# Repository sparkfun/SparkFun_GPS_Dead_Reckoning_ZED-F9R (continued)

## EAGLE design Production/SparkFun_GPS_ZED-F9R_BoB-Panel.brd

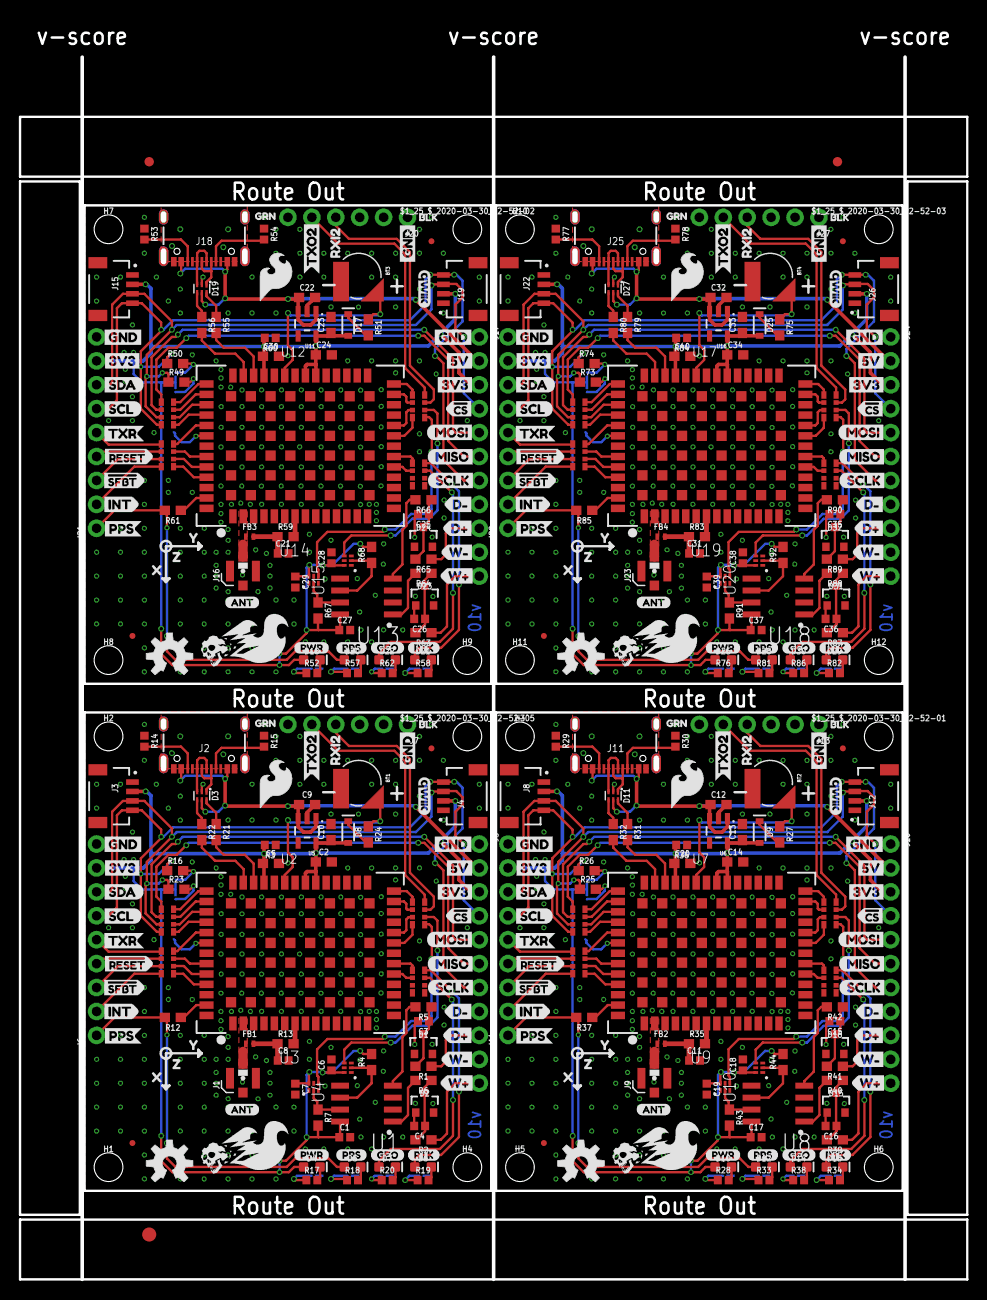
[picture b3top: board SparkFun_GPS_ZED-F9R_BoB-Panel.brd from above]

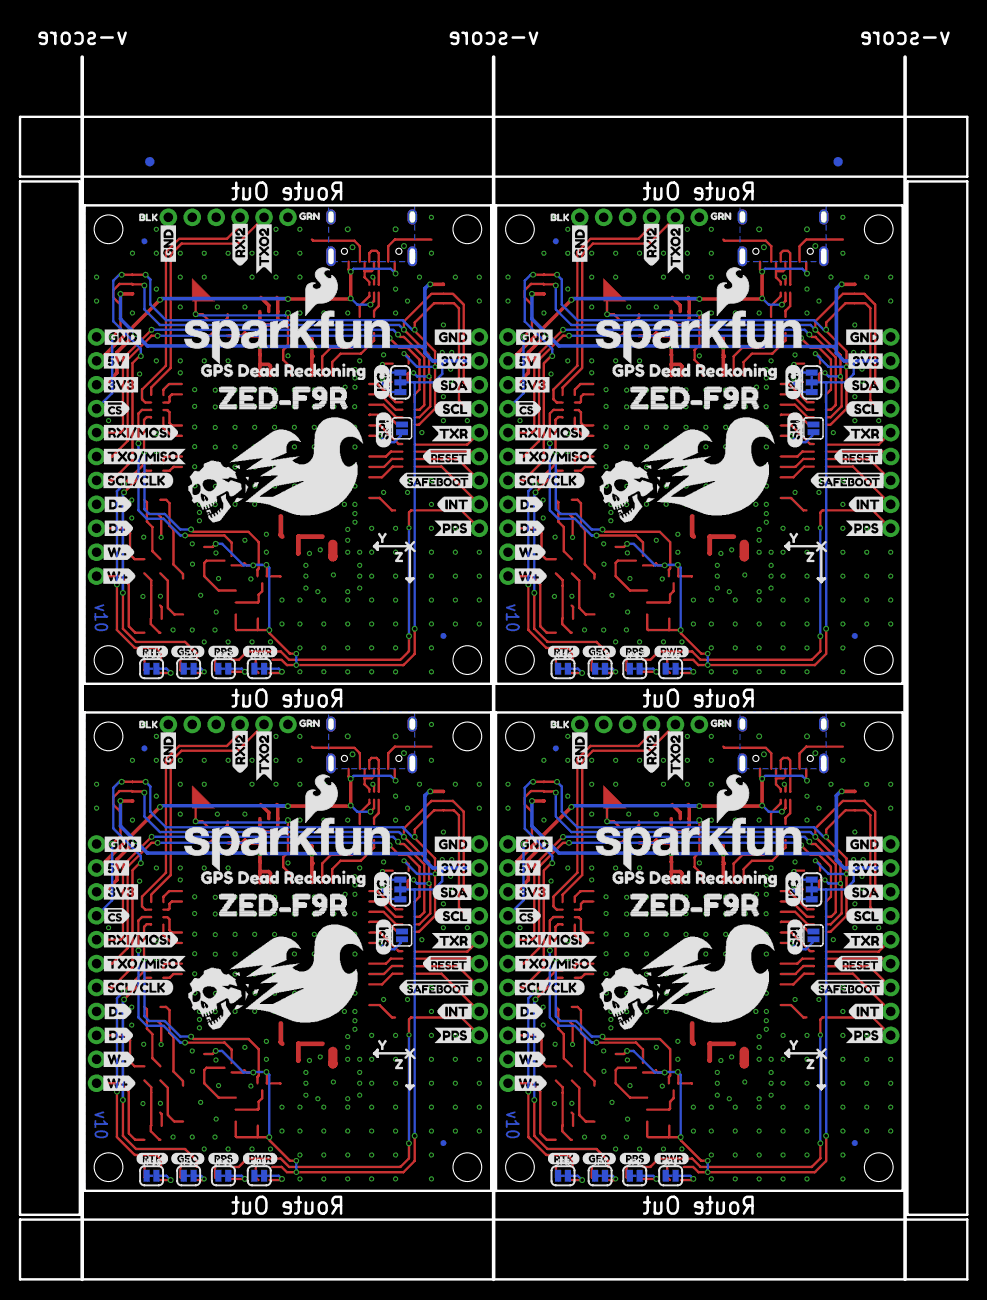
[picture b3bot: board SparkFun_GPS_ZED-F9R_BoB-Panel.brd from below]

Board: 2 copper layers, 100.6 x 129.8 mm, 581 parts (182 on the bottom side), 264 nets.

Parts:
$1_25_$_2020-03-30_22-52-01, $1_25_$_2020-03-30_22-52-02, $1_25_$_2020-03-30_22-52-03, $1_25_$_2020-03-30_22-52-05: STAND-OFFTIGHT; STAND-OFF-TIGHT
BT1, BT2, BT3, BT4: ML414H_IV01E_BATTERY; ML414H_IV01E
C1, C6, C7, C17, C18, C19, C27, C28, C29, C37, C38, C39: 0.1uF; 0402
C2, C5, C9, C10, C12, C13, C14, C20, C22, C23, C24, C30, C32, C33, C34, C40: 1.0uF; 0603
C3, C4, C15, C16, C25, C26, C35, C36: 1nF; 0402
C8, C11, C21, C31: 47pF; 0402
D1, D2, D15, D16, D23, D24, D31, D32: 15V; SOT23-3
D3, D11, D19, D27: PRTR5V0U2F; SOT886
D4, D10, D18, D26: RED; LED-0603
D5, D6, D7, D12, D13, D14, D20, D21, D22, D28, D29, D30: BLUE; LED-0603
D8, D9, D17, D25: 0.5A/40V/420mV; SOD-323
E$1, E$2, E$3, E$4: FIDUCIAL-1X2
E$5: FIDUCIAL-1.5X3
FB1, FB2, FB3, FB4: 120NH; 0402_MURATA
FD1, FD2, FD3, FD4, FD5, FD6, FD7, FD8, FD9, FD10, FD11, FD12, FD13, FD14, FD15, FD16: FIDUCIALUFIDUCIAL; FIDUCIAL-MICRO
H1, H2, H3, H4, H5, H6, H7, H8, H9, H10, H11, H12: STAND-OFFTIGHT; STAND-OFF-TIGHT
J1, J9, J16, J23: U.FL
J2, J11, J18, J25: USB-C-16P-2LAYER-PADS
J3, J4, J8, J12, J15, J19, J22, J26: QWIIC_RIGHT_ANGLE; JST04_1MM_RA
J5, J10, J17, J24: 1X11_NO_SILK
J6, J14, J21, J28: 1X09_NO_SILK
J7, J13, J20, J27: 1X06_NO_SILK
JP1, JP2, JP3, JP4, JP9, JP10, JP11, JP12, JP15, JP16, JP17, JP18, JP21, JP22, JP23, JP24: JUMPER-SMT_2_NC_TRACE_SILK; SMT-JUMPER_2_NC_TRACE_SILK
JP5, JP8, JP14, JP20: JUMPER-SMT_2_NO_SILK; SMT-JUMPER_2_NO_SILK
JP6, JP7, JP13, JP19: JUMPER-SMT_3_2-NC_TRACE_SILK; SMT-JUMPER_3_2-NC_TRACE_SILK
LOGO1, LOGO6, LOGO9, LOGO12: OSHW-LOGOM; OSHW-LOGO-M
LOGO2, LOGO5, LOGO8, LOGO11: QWIIC_LOGO_4MM; QWIIC_4MM
LOGO3, LOGO4, LOGO7, LOGO10: SFE_LOGO_NAME_FLAME.2_INCH; SFE_LOGO_NAME_FLAME_.2
R1, R2, R24, R27, R39, R41, R51, R63, R65, R75, R87, R89: 3.3k; 0603
R3, R36, R60, R84: 100K; 0402
R4, R7, R43, R44, R67, R68, R91, R92: 910; 0603
R5, R6, R40, R42, R64, R66, R88, R90: 470; 0603
R8, R9, R10, R11, R45, R46, R47, R48, R69, R70, R71, R72, R93, R94, R95, R96: 33; 1206_RA
R12, R13, R35, R37, R59, R61, R83, R85: 33; 0603
R14, R15, R29, R30, R53, R54, R77, R78: 5.1k; 0402
R16, R23, R25, R26, R49, R50, R73, R74: 2.2k; 0603
R17, R18, R19, R20, R28, R33, R34, R38, R52, R57, R58, R62, R76, R81, R82, R86: 1KOHM-0402-1/16W-1%; 0402
R21, R22, R31, R32, R55, R56, R79, R80: 27; 0603
U1, U8, U13, U18: DUAL-OPTO_HCPL-073L; SOP_8-PIN
U2, U7, U12, U17: U-BLOX_ZED_F9R; UBLOX_ZED_F9R
U3, U4, U9, U10, U14, U15, U19, U20: UHS_INVERTER_SCHMITT_TRIGGERSIP6; SIP6
U5, U6, U11, U16: 3.3V; SOT23-5
U$1, U$29, U$40, U$70, U$78, U$80, U$113, U$115, U$149, U$151, U$184, U$186, U$220, U$222, U$255, U$257: 3V3-04
U$2, U$15, U$31, U$34, U$41, U$71, U$79, U$81, U$83, U$114, U$116, U$126, U$150, U$152, U$154, U$185, U$187, U$197, U$221, U$223, U$225, U$256, U$258, U$268: GND-04
U$3, U$60, U$119, U$139, U$190, U$210, U$261, U$281: D#0
U$4, U$47, U$73, U$89, U$144, U$160, U$215, U$231: PPS8
U$5, U$48, U$74, U$90, U$145, U$161, U$216, U$232: PWR10
U$6, U$64, U$120, U$141, U$191, U$212, U$262, U$283: D#1
U$7, U$105, U$176, U$247: #RESET2
U$8, U$22, U$75, U$88, U$146, U$159, U$217, U$230: RTK9
U$9, U$61, U$121, U$140, U$192, U$211, U$263, U$282: W#2
U$10, U$65, U$122, U$142, U$193, U$213, U$264, U$284: W#3
U$11, U$33, U$82, U$123, U$153, U$194, U$224, U$265: 5V
U$12, U$124, U$195, U$266: INT1
U$13, U$125, U$196, U$267: PPS4
U$14, U$128, U$199, U$270: RXI22
U$16, U$36, U$85, U$127, U$156, U$198, U$227, U$269: TXO21
U$17, U$129, U$200, U$271: SCLK1
U$18, U$130, U$201, U$272: TXR0
U$19, U$20, U$132, U$133, U$203, U$204, U$274, U$275: DEAD#RECKONING#GPS#BOARD#SILK#FINAL#JPG
U$21, U$54, U$76, U$94, U$147, U$165, U$218, U$236: BLK2
U$23, U$53, U$77, U$93, U$148, U$164, U$219, U$235: GRN1
U$24, U$95, U$166, U$237: INT2
U$25, U$131, U$202, U$273: GPS_DEAD_RECKONING0
U$26, U$72, U$143, U$214: CS#-<]-04
U$27, U$96, U$167, U$238: PPS1
U$28, U$106, U$177, U$248: #SAFEBOOT3
U$30, U$98, U$169, U$240: RXI#MOSI0
U$32, U$134, U$205, U$276: X1
U$35, U$84, U$155, U$226: RXI28
U$37, U$99, U$170, U$241: TXO#MISO1
U$38, U$100, U$171, U$242: SCL#CLK2
U$39, U$101, U$172, U$243: SCL5
U$42, U$102, U$173, U$244: SDA4
U$43, U$103, U$174, U$245: TXR3
U$44, U$104, U$175, U$246: #RESET1
U$45, U$86, U$157, U$228: SPI4
U$46, U$87, U$158, U$229: I_SUPER2_C-()-04
U$49, U$91, U$162, U$233: ANT0
U$50, U$52, U$135, U$136, U$206, U$207, U$277, U$278: Y2
U$51, U$92, U$163, U$234: ZED#F9R0
U$55, U$107, U$178, U$249: #SFBT0
U$56, U$58, U$108, U$109, U$179, U$180, U$250, U$251: GEO1
U$57, U$63, U$137, U$138, U$208, U$209, U$279, U$280: Z0
U$59, U$97, U$168, U$239: CS#-[>-04
U$62, U$110, U$181, U$252: SFE_LOGO_FLAME_.2
U$66, U$117, U$188, U$259: MISO-(]-04
U$67, U$111, U$182, U$253: SCL-[)
U$68, U$112, U$183, U$254: SDA-[)
U$69, U$118, U$189, U$260: MOSI-(]-04

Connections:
3.3V: C1.1, C2.1, C5.1, C6.1, C7.1, C10.1, D4.A, D8.A, J3.2, J4.2, J5.3, J6.8, JP6.2, R3.2, R4.2, R7.2, U1.P8, U2.P33, U2.P34, U2.P38, U3.P6, U4.P6, U5.5
3.3V1: C13.1, C14.1, C17.1, C18.1, C19.1, C20.1, D9.A, D10.A, J8.2, J10.3, J12.2, J14.8, JP7.2, R36.2, R43.2, R44.2, U6.5, U7.P33, U7.P34, U7.P38, U8.P8, U9.P6, U10.P6
3.3V2: C23.1, C24.1, C27.1, C28.1, C29.1, C30.1, D17.A, D18.A, J15.2, J17.3, J19.2, J21.8, JP13.2, R60.2, R67.2, R68.2, U11.5, U12.P33, U12.P34, U12.P38, U13.P8, U14.P6, U15.P6
3.3V3: C33.1, C34.1, C37.1, C38.1, C39.1, C40.1, D25.A, D26.A, J22.2, J24.3, J26.2, J28.8, JP19.2, R84.2, R91.2, R92.2, U16.5, U17.P33, U17.P34, U17.P38, U18.P8, U19.P6, U20.P6
!RESET: J6.4, R8.P2
!RESET1: J14.4, R46.P2
!RESET2: J21.4, R70.P2
!RESET3: J28.4, R94.P2
!SAFEBOOT: J6.3, R8.P3
!SAFEBOOT1: J14.3, R46.P3
!SAFEBOOT2: J21.3, R70.P3
!SAFEBOOT3: J28.3, R94.P3
DIR+: J5.9, R1.1
DIR+1: J10.9, R41.1
DIR+2: J17.9, R65.1
DIR+3: J24.9, R89.1
DIR_IN: R5.2, U1.P4
DIR_IN1: R42.2, U8.P4
DIR_IN2: R66.2, U13.P4
DIR_IN3: R90.2, U18.P4
DIR_OUT: R10.P6, U4.P4
DIR_OUT1: R47.P6, U10.P4
DIR_OUT2: R71.P6, U15.P4
DIR_OUT3: R95.P6, U20.P4
DIR_SCHMITT: R4.1, U1.P6, U4.P2
DIR_SCHMITT1: R44.1, U8.P6, U10.P2
DIR_SCHMITT2: R68.1, U13.P6, U15.P2
DIR_SCHMITT3: R92.1, U18.P6, U20.P2
DMINUS: R21.2, U2.P39
DMINUS1: R31.2, U7.P39
DMINUS2: R55.2, U12.P39
DMINUS3: R79.2, U17.P39
DPLUS: R22.2, U2.P40
DPLUS1: R32.2, U7.P40
DPLUS2: R56.2, U12.P40
DPLUS3: R80.2, U17.P40
D_SEL: JP5.1, U2.P47
D_SEL1: JP8.1, U7.P47
D_SEL2: JP14.1, U12.P47
D_SEL3: JP20.1, U17.P47
GEOF_STAT: D7.A, R11.P7
GEOF_STAT1: D14.A, R48.P7
GEOF_STAT2: D22.A, R72.P7
GEOF_STAT3: D30.A, R96.P7
GND: BT1.-, C1.2, C2.2, C3.2, C4.2, C5.2, C6.2, C7.2, C8.2, C9.2, C10.2, D1.1, D2.1, D3.2, J1.1, J1.2, J2.GND, J2.GND2, J3.1, J4.1, J5.1, J5.8, J5.10, J6.9, J7.1, JP1.1, JP2.1, JP3.1, JP4.1, JP5.2, R3.1, R14.1, R15.1, U1.P2, U1.P3, U1.P5, U2.G1, U2.G2, U2.G3, U2.G4, U2.G5, U2.G6, U2.G7, U2.G8, U2.G9, U2.G10, U2.G11, U2.G12, U2.G13, U2.G14, U2.G15, U2.G16, U2.G17, U2.G18, U2.G19, U2.G20, U2.G21, U2.G22, U2.G23, U2.G24, U2.G25, U2.G26, U2.G27, U2.G28, U2.G29, U2.G30, U2.G31, U2.G32, U2.G33, U2.G34, U2.G35, U2.G36, U2.G37, U2.G38, U2.G39, U2.G40, U2.G41, U2.G42, U2.G43, U2.G44, U2.G45, U2.G46, U2.G47, U2.G48, U2.P1, U2.P3, U2.P12, U2.P14, U2.P32, U2.P37, U2.P41, U2.P48, U3.P3, U4.P3, U5.2
GND1: BT2.-, C11.2, C12.2, C13.2, C14.2, C15.2, C16.2, C17.2, C18.2, C19.2, C20.2, D11.2, D15.1, D16.1, J8.1, J9.1, J9.2, J10.1, J10.8, J10.10, J11.GND, J11.GND2, J12.1, J13.1, J14.9, JP8.2, JP9.1, JP10.1, JP11.1, JP12.1, R29.1, R30.1, R36.1, U6.2, U7.G1, U7.G2, U7.G3, U7.G4, U7.G5, U7.G6, U7.G7, U7.G8, U7.G9, U7.G10, U7.G11, U7.G12, U7.G13, U7.G14, U7.G15, U7.G16, U7.G17, U7.G18, U7.G19, U7.G20, U7.G21, U7.G22, U7.G23, U7.G24, U7.G25, U7.G26, U7.G27, U7.G28, U7.G29, U7.G30, U7.G31, U7.G32, U7.G33, U7.G34, U7.G35, U7.G36, U7.G37, U7.G38, U7.G39, U7.G40, U7.G41, U7.G42, U7.G43, U7.G44, U7.G45, U7.G46, U7.G47, U7.G48, U7.P1, U7.P3, U7.P12, U7.P14, U7.P32, U7.P37, U7.P41, U7.P48, U8.P2, U8.P3, U8.P5, U9.P3, U10.P3
GND2: BT3.-, C21.2, C22.2, C23.2, C24.2, C25.2, C26.2, C27.2, C28.2, C29.2, C30.2, D19.2, D23.1, D24.1, J15.1, J16.1, J16.2, J17.1, J17.8, J17.10, J18.GND, J18.GND2, J19.1, J20.1, J21.9, JP14.2, JP15.1, JP16.1, JP17.1, JP18.1, R53.1, R54.1, R60.1, U11.2, U12.G1, U12.G2, U12.G3, U12.G4, U12.G5, U12.G6, U12.G7, U12.G8, U12.G9, U12.G10, U12.G11, U12.G12, U12.G13, U12.G14, U12.G15, U12.G16, U12.G17, U12.G18, U12.G19, U12.G20, U12.G21, U12.G22, U12.G23, U12.G24, U12.G25, U12.G26, U12.G27, U12.G28, U12.G29, U12.G30, U12.G31, U12.G32, U12.G33, U12.G34, U12.G35, U12.G36, U12.G37, U12.G38, U12.G39, U12.G40, U12.G41, U12.G42, U12.G43, U12.G44, U12.G45, U12.G46, U12.G47, U12.G48, U12.P1, U12.P3, U12.P12, U12.P14, U12.P32, U12.P37, U12.P41, U12.P48, U13.P2, U13.P3, U13.P5, U14.P3, U15.P3
GND3: BT4.-, C31.2, C32.2, C33.2, C34.2, C35.2, C36.2, C37.2, C38.2, C39.2, C40.2, D27.2, D31.1, D32.1, J22.1, J23.1, J23.2, J24.1, J24.8, J24.10, J25.GND, J25.GND2, J26.1, J27.1, J28.9, JP20.2, JP21.1, JP22.1, JP23.1, JP24.1, R77.1, R78.1, R84.1, U16.2, U17.G1, U17.G2, U17.G3, U17.G4, U17.G5, U17.G6, U17.G7, U17.G8, U17.G9, U17.G10, U17.G11, U17.G12, U17.G13, U17.G14, U17.G15, U17.G16, U17.G17, U17.G18, U17.G19, U17.G20, U17.G21, U17.G22, U17.G23, U17.G24, U17.G25, U17.G26, U17.G27, U17.G28, U17.G29, U17.G30, U17.G31, U17.G32, U17.G33, U17.G34, U17.G35, U17.G36, U17.G37, U17.G38, U17.G39, U17.G40, U17.G41, U17.G42, U17.G43, U17.G44, U17.G45, U17.G46, U17.G47, U17.G48, U17.P1, U17.P3, U17.P12, U17.P14, U17.P32, U17.P37, U17.P41, U17.P48, U18.P2, U18.P3, U18.P5, U19.P3, U20.P3
INT: J6.2, R8.P4
INT1: J14.2, R46.P4
INT2: J21.2, R70.P4
INT3: J28.2, R94.P4
unnamed: JP6.1, R23.2
unnamed: D8.C, R24.2
unnamed: JP6.3, R16.2
unnamed: D4.C, R17.2
unnamed: C8.1, FB1.P2, R13.1
unnamed: D3.3, J2.A6, J2.B6
unnamed: D3.1, J2.A7, J2.B7
unnamed: JP1.2, R17.1
unnamed: D3.6, R21.1
unnamed: D3.4, R22.1
unnamed: R8.P7, U2.P49
unnamed: R8.P5, U2.P51
unnamed: D9.C, R27.2
unnamed: J2.B5, R14.2
unnamed: J2.A5, R15.2
unnamed: R9.P6, U2.P44
unnamed: R9.P5, U2.P45
unnamed: R8.P8, U2.P46
unnamed: R9.P8, U2.P42
unnamed: R9.P7, U2.P43
unnamed: R10.P1, U2.P27
unnamed: JP3.2, R19.1
unnamed: JP2.2, R18.1
unnamed: D5.C, R18.2
unnamed: D6.C, R19.2
unnamed: R10.P2, U2.P26
unnamed: R11.P2, U2.P19
unnamed: R11.P1, U2.P20
unnamed: R12.1, U2.P53
unnamed: R8.P6, U2.P50
unnamed: R10.P4, U2.P22
unnamed: R10.P3, U2.P23
unnamed: JP4.2, R20.1
unnamed: D7.C, R20.2
unnamed: C4.1, D2.3, R2.2, R6.1
unnamed: JP7.1, R25.2
unnamed: C3.1, D1.3, R1.2, R5.1
unnamed: JP7.3, R26.2
unnamed: J11.B5, R29.2
unnamed: J11.A5, R30.2
unnamed: JP10.2, R34.1
unnamed: JP11.2, R33.1
unnamed: D12.C, R33.2
unnamed: D13.C, R34.2
unnamed: D10.C, R28.2
unnamed: JP9.2, R28.1
unnamed: C11.1, FB2.P2, R35.1
unnamed: D11.3, J11.A6, J11.B6
unnamed: D11.1, J11.A7, J11.B7
unnamed: D11.6, R31.1
unnamed: D11.4, R32.1
unnamed: R46.P7, U7.P49
unnamed: R46.P5, U7.P51
unnamed: R45.P6, U7.P44
unnamed: R45.P5, U7.P45
unnamed: R46.P8, U7.P46
unnamed: R45.P8, U7.P42
unnamed: R45.P7, U7.P43
unnamed: R47.P1, U7.P27
unnamed: R47.P2, U7.P26
unnamed: R48.P2, U7.P19
unnamed: R48.P1, U7.P20
unnamed: R37.1, U7.P53
unnamed: R46.P6, U7.P50
unnamed: R47.P4, U7.P22
unnamed: R47.P3, U7.P23
unnamed: JP12.2, R38.1
unnamed: D14.C, R38.2
unnamed: C16.1, D15.3, R39.2, R40.1
unnamed: C15.1, D16.3, R41.2, R42.1
unnamed: D17.C, R51.2
unnamed: JP13.1, R49.2
unnamed: JP13.3, R50.2
unnamed: J18.B5, R53.2
unnamed: J18.A5, R54.2
unnamed: JP16.2, R58.1
unnamed: JP17.2, R57.1
unnamed: D20.C, R57.2
unnamed: D21.C, R58.2
unnamed: D18.C, R52.2
unnamed: JP15.2, R52.1
unnamed: C21.1, FB3.P2, R59.1
unnamed: D19.3, J18.A6, J18.B6
unnamed: D19.1, J18.A7, J18.B7
unnamed: D19.6, R55.1
unnamed: D19.4, R56.1
unnamed: R70.P7, U12.P49
unnamed: R70.P5, U12.P51
unnamed: R69.P6, U12.P44
unnamed: R69.P5, U12.P45
unnamed: R70.P8, U12.P46
unnamed: R69.P8, U12.P42
unnamed: R69.P7, U12.P43
unnamed: R71.P1, U12.P27
unnamed: R71.P2, U12.P26
unnamed: R72.P2, U12.P19
unnamed: R72.P1, U12.P20
unnamed: R61.1, U12.P53
unnamed: R70.P6, U12.P50
unnamed: R71.P4, U12.P22
unnamed: R71.P3, U12.P23
unnamed: JP18.2, R62.1
unnamed: D22.C, R62.2
unnamed: C26.1, D23.3, R63.2, R64.1
unnamed: C25.1, D24.3, R65.2, R66.1
unnamed: D25.C, R75.2
unnamed: JP19.1, R73.2
unnamed: JP19.3, R74.2
unnamed: J25.B5, R77.2
unnamed: J25.A5, R78.2
unnamed: JP22.2, R82.1
unnamed: JP23.2, R81.1
unnamed: D28.C, R81.2
unnamed: D29.C, R82.2
unnamed: D26.C, R76.2
unnamed: JP21.2, R76.1
unnamed: C31.1, FB4.P2, R83.1
unnamed: D27.3, J25.A6, J25.B6
unnamed: D27.1, J25.A7, J25.B7
unnamed: D27.6, R79.1
unnamed: D27.4, R80.1
unnamed: R94.P7, U17.P49
unnamed: R94.P5, U17.P51
unnamed: R93.P6, U17.P44
unnamed: R93.P5, U17.P45
unnamed: R94.P8, U17.P46
unnamed: R93.P8, U17.P42
unnamed: R93.P7, U17.P43
unnamed: R95.P1, U17.P27
unnamed: R95.P2, U17.P26
unnamed: R96.P2, U17.P19
unnamed: R96.P1, U17.P20
unnamed: R85.1, U17.P53
unnamed: R94.P6, U17.P50
unnamed: R95.P4, U17.P22
unnamed: R95.P3, U17.P23
unnamed: JP24.2, R86.1
unnamed: D30.C, R86.2
unnamed: C36.1, D31.3, R87.2, R88.1
unnamed: C35.1, D32.3, R89.2, R90.1
PPS: D5.A, J6.1, R12.2
PPS1: D12.A, J14.1, R37.2
PPS2: D20.A, J21.1, R61.2
PPS3: D28.A, J28.1, R85.2
RF_IN: FB1.P1, J1.FEED, U2.P2
RF_IN1: FB2.P1, J9.FEED, U7.P2
RF_IN2: FB3.P1, J16.FEED, U12.P2
RF_IN3: FB4.P1, J23.FEED, U17.P2
RTK_STAT: D6.A, R11.P8
RTK_STAT1: D13.A, R48.P8
RTK_STAT2: D21.A, R72.P8
RTK_STAT3: D29.A, R96.P8
RXI1: J13.4, R47.P7
RXI2: J7.4, R10.P7
RXI3: J20.4, R71.P7
RXI4: J27.4, R95.P7
RXI/MOSI: J5.5, R9.P2
RXI/MOSI1: J10.5, R45.P2
RXI/MOSI2: J17.5, R69.P2
RXI/MOSI3: J24.5, R93.P2
SCL/CLK: J3.4, J4.4, J5.7, J6.6, R9.P4, R16.1
SCL/CLK1: J8.4, J10.7, J12.4, J14.6, R26.1, R45.P4
SCL/CLK2: J15.4, J17.7, J19.4, J21.6, R50.1, R69.P4
SCL/CLK3: J22.4, J24.7, J26.4, J28.6, R74.1, R93.P4
SDA/!CS: J3.3, J4.3, J5.4, J6.7, R9.P3, R23.1
SDA/!CS1: J8.3, J10.4, J12.3, J14.7, R25.1, R45.P3
SDA/!CS2: J15.3, J17.4, J19.3, J21.7, R49.1, R69.P3
SDA/!CS3: J22.3, J24.4, J26.3, J28.7, R73.1, R93.P3
SHIELD: J2.SHLD1, J2.SHLD2, J2.SHLD3, J2.SHLD4
SHIELD1: J11.SHLD1, J11.SHLD2, J11.SHLD3, J11.SHLD4
SHIELD2: J18.SHLD1, J18.SHLD2, J18.SHLD3, J18.SHLD4
SHIELD3: J25.SHLD1, J25.SHLD2, J25.SHLD3, J25.SHLD4
TXO1: J13.5, R47.P8
TXO2: J7.5, R10.P8
TXO3: J20.5, R71.P8
TXO4: J27.5, R95.P8
TXO/MISO: J5.6, R9.P1
TXO/MISO1: J10.6, R45.P1
TXO/MISO2: J17.6, R69.P1
TXO/MISO3: J24.6, R93.P1
TX_READY: J6.5, R8.P1
TX_READY1: J14.5, R46.P1
TX_READY2: J21.5, R70.P1
TX_READY3: J28.5, R94.P1
VIN: C9.1, D3.5, J2.VBUS1, J2.VBUS2, J5.2, U5.1, U5.3
VIN1: C12.1, D11.5, J10.2, J11.VBUS1, J11.VBUS2, U6.1, U6.3
VIN2: C22.1, D19.5, J17.2, J18.VBUS1, J18.VBUS2, U11.1, U11.3
VIN3: C32.1, D27.5, J24.2, J25.VBUS1, J25.VBUS2, U16.1, U16.3
V_BATT: BT1.+, R24.1, U2.P36
V_BATT1: BT2.+, R27.1, U7.P36
V_BATT2: BT3.+, R51.1, U12.P36
V_BATT3: BT4.+, R75.1, U17.P36
V_RF: R13.2, U2.P7
V_RF1: R35.2, U7.P7
V_RF2: R59.2, U12.P7
V_RF3: R83.2, U17.P7
WT+: J5.11, R2.1
WT+1: J10.11, R39.1
WT+2: J17.11, R63.1
WT+3: J24.11, R87.1
WT_IN: R6.2, U1.P1
WT_IN1: R40.2, U8.P1
WT_IN2: R64.2, U13.P1
WT_IN3: R88.2, U18.P1
WT_OUT: R10.P5, U3.P4
WT_OUT1: R47.P5, U9.P4
WT_OUT2: R71.P5, U14.P4
WT_OUT3: R95.P5, U19.P4
WT_SCHMITT: R7.1, U1.P7, U3.P2
WT_SCHMITT1: R43.1, U8.P7, U9.P2
WT_SCHMITT2: R67.1, U13.P7, U14.P2
WT_SCHMITT3: R91.1, U18.P7, U19.P2

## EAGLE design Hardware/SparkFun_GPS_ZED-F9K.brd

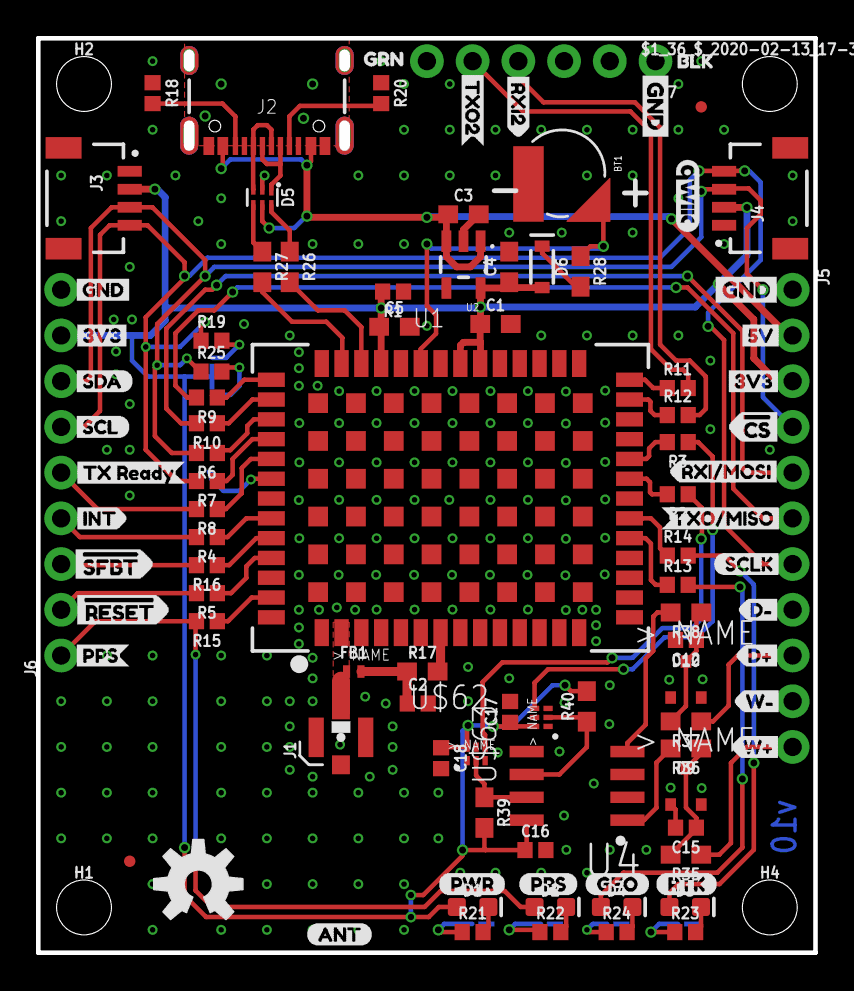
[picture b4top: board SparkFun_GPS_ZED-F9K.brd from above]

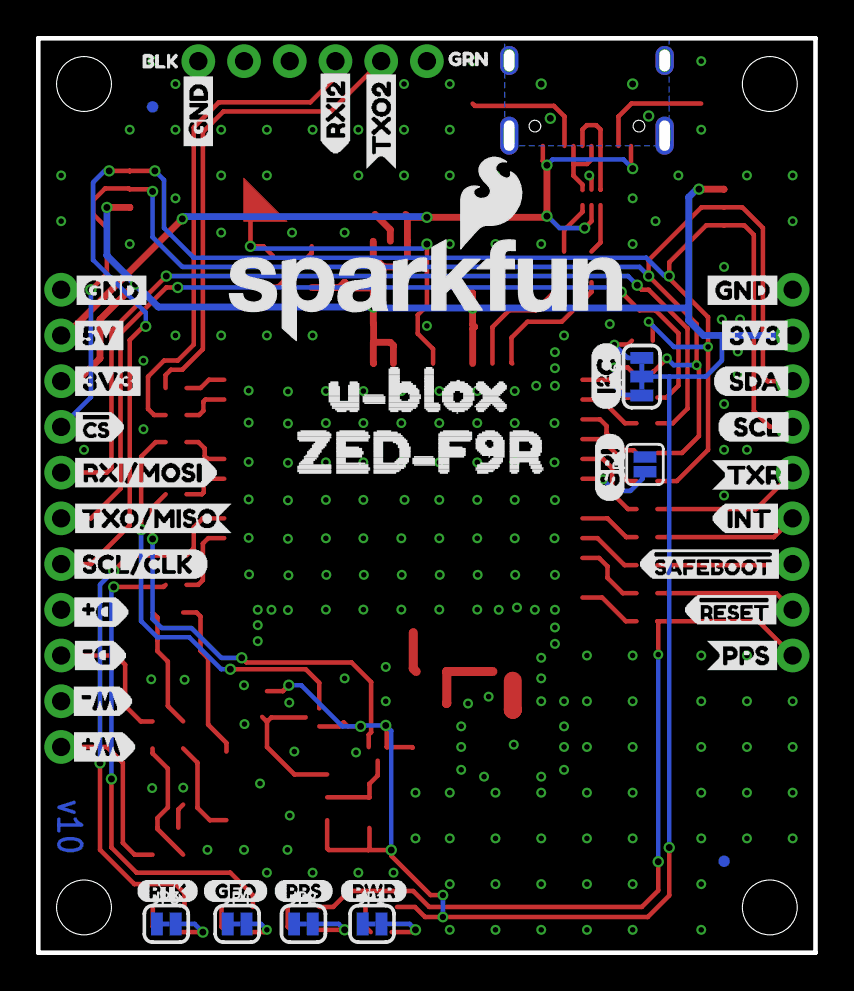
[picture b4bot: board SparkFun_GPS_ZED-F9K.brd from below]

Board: 2 copper layers, 43.2 x 50.8 mm, 147 parts (42 on the bottom side), 66 nets.

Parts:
$1_36_$_2020-02-13_17-32-45: STAND-OFFTIGHT; STAND-OFF-TIGHT
BT1: ML414H_IV01E_BATTERY; ML414H_IV01E
C1, C3, C4, C5: 1.0uF; 0603
C2: 47pF; 0402
C12, C15: 1nF; 0402
C16, C17, C18: 0.1uF; 0402
D1: RED; LED-0603
D2, D3, D4: BLUE; LED-0603
D5: PRTR5V0U2F; SOT886
D6: 0.5A/40V/420mV; SOD-323
D9, D10: 0.5A/40V/420mV; SOT23_BZX
FB1: 120NH; 0402_MURATA
FD1, FD2, FD3, FD4: FIDUCIALUFIDUCIAL; FIDUCIAL-MICRO
FRAME1: FRAME-LEDGER; CREATIVE_COMMONS
H1, H2, H4: STAND-OFFTIGHT; STAND-OFF-TIGHT
J1: U.FL
J2: USB-C-16P-2LAYER-PADS
J3, J4: QWIIC_RIGHT_ANGLE; JST04_1MM_RA
J5: 1X11_NO_SILK
J6: 1X09_NO_SILK
J7: 1X06_NO_SILK
JP1, JP2, JP3, JP4: JUMPER-SMT_2_NC_TRACE_SILK; SMT-JUMPER_2_NC_TRACE_SILK
JP5: JUMPER-SMT_2_NO_SILK; SMT-JUMPER_2_NO_SILK
JP6: JUMPER-SMT_3_2-NC_TRACE_SILK; SMT-JUMPER_3_2-NC_TRACE_SILK
LOGO1: OSHW-LOGOM; OSHW-LOGO-M
LOGO2: QWIIC_LOGO_4MM; QWIIC_4MM
LOGO3: SFE_LOGO_NAME_FLAME.2_INCH; SFE_LOGO_NAME_FLAME_.2
R1: 100K; 0402
R2, R3, R4, R5, R6, R7, R8, R9, R10, R11, R12, R13, R14, R15, R16: 33; 0402
R17: 33; 0603
R18, R20: 5.1k; 0402
R19, R25: 2.2K; 0402
R21, R22, R23, R24: 1KOHM-0402-1/16W-1%; 0402
R26, R27: 27; 0603
R28, R35, R37: 3.3k; 0603
R36, R38: 470; 0603
R39, R40: 910; 0603
U1: UBLOX_ZED_F9R
U2: 3.3V; SOT23-5
U4: HCPL-270L; SOP_8-PIN
U$1, U$24: INT2
U$2: PPS4
U$3, U$19: 3V32
U$4, U$47: PPS8
U$5, U$48: PWR10
U$6: GND3
U$7: #RESET2
U$8, U$22: RTK9
U$9: RXI#MOSI5
U$10, U$60: D#0
U$11: SCL0
U$12: SDA1
U$13, U$61: D#1
U$14: RXI22
U$15: TXO#MISO6
U$16: TX_READY0
U$17, U$20: GND-03
U$18: 5V0
U$21, U$54: BLK2
U$23, U$53: GRN1
U$25, U$36: TXO21
U$26: CS#-<]-04
U$27: PPS1
U$28: #SAFEBOOT3
U$29, U$40: 3V3-04
U$30: RXI#MOSI0
U$31, U$34, U$41: GND-04
U$32, U$64: W#2
U$33: 5V
U$35: RXI28
U$37: TXO#MISO1
U$38: SCL#CLK2
U$39: SCL5
U$42: SDA4
U$43: TXR3
U$44: #RESET1
U$45: SPI4
U$46: I_SUPER2_C-()-04
U$49: ANT0
U$50, U$65: W#3
U$51: ZED#F9R0
U$52: U#BLOX1
U$55: #SFBT0
U$56, U$58: GEO1
U$57: SCLK2
U$59: CS#-[>-04
U$62, U$63: UHS_INVERTER_SCHMITT_TRIGGERSIP6; SIP6

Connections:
3.3V: C1.1, C4.1, C5.1, C16.1, C17.1, C18.1, D1.A, D6.A, J3.2, J4.2, J5.3, J6.8, JP6.2, R1.2, R39.2, R40.2, U1.P33, U1.P34, U1.P38, U2.5, U4.P8, U$62.P6, U$63.P6
!RESET: J6.4, R4.2
!SAFEBOOT: J6.3, R16.2
DIR+: J5.9, R37.1
DIR_IN: R38.2, U4.P4
DIR_OUT: R3.1, U$63.P4
DIR_SCHMITT: R40.1, U4.P6, U$63.P2
DMINUS: R26.2, U1.P39
DPLUS: R27.2, U1.P40
D_SEL: JP5.1, U1.P47
GEOF_STAT: D4.A, R13.2
GND: BT1.-, C1.2, C2.2, C3.2, C4.2, C5.2, C12.2, C15.2, C16.2, C17.2, C18.2, D5.2, D9.P1, D10.P1, J1.1, J1.2, J2.GND, J2.GND2, J3.1, J4.1, J5.1, J5.8, J5.10, J6.9, J7.1, JP1.1, JP2.1, JP3.1, JP4.1, JP5.2, R1.1, R18.1, R20.1, U1.G1, U1.G2, U1.G3, U1.G4, U1.G5, U1.G6, U1.G7, U1.G8, U1.G9, U1.G10, U1.G11, U1.G12, U1.G13, U1.G14, U1.G15, U1.G16, U1.G17, U1.G18, U1.G19, U1.G20, U1.G21, U1.G22, U1.G23, U1.G24, U1.G25, U1.G26, U1.G27, U1.G28, U1.G29, U1.G30, U1.G31, U1.G32, U1.G33, U1.G34, U1.G35, U1.G36, U1.G37, U1.G38, U1.G39, U1.G40, U1.G41, U1.G42, U1.G43, U1.G44, U1.G45, U1.G46, U1.G47, U1.G48, U1.P1, U1.P3, U1.P12, U1.P14, U1.P32, U1.P37, U1.P41, U1.P48, U2.2, U4.P2, U4.P3, U4.P5, U$62.P3, U$63.P3
INT: J6.2, R5.2
unnamed: JP6.1, R25.2
unnamed: D6.C, R28.2
unnamed: JP6.3, R19.2
unnamed: D1.C, R21.2
unnamed: C2.1, FB1.P2, R17.1
unnamed: D5.3, J2.A6, J2.B6
unnamed: D5.1, J2.A7, J2.B7
unnamed: JP1.2, R21.1
unnamed: D5.6, R26.1
unnamed: D5.4, R27.1
unnamed: R4.1, U1.P49
unnamed: R5.1, U1.P51
unnamed: J2.B5, R18.2
unnamed: J2.A5, R20.2
unnamed: R6.1, U1.P44
unnamed: R7.1, U1.P45
unnamed: R8.1, U1.P46
unnamed: R9.1, U1.P42
unnamed: R10.1, U1.P43
unnamed: R11.1, U1.P27
unnamed: JP3.2, R23.1
unnamed: JP2.2, R22.1
unnamed: D2.C, R22.2
unnamed: D3.C, R23.2
unnamed: R12.1, U1.P26
unnamed: R13.1, U1.P19
unnamed: R14.1, U1.P20
unnamed: R15.1, U1.P53
unnamed: R16.1, U1.P50
unnamed: R2.2, U1.P22
unnamed: R3.2, U1.P23
unnamed: JP4.2, R24.1
unnamed: D4.C, R24.2
unnamed: C15.1, D9.P3, R35.2, R36.1
unnamed: C12.1, D10.P3, R37.2, R38.1
PPS: D2.A, J6.1, R15.2
RF_IN: FB1.P1, J1.FEED, U1.P2
RTK_STAT: D3.A, R14.2
RXI2: J7.4, R12.2
RXI/MOSI: J5.5, R10.2
SCL/CLK: J3.4, J4.4, J5.7, J6.6, R7.2, R19.1
SDA/!CS: J3.3, J4.3, J5.4, J6.7, R6.2, R25.1
SHIELD: J2.SHLD1, J2.SHLD2, J2.SHLD3, J2.SHLD4
TXO2: J7.5, R11.2
TXO/MISO: J5.6, R9.2
TX_READY: J6.5, R8.2
VIN: C3.1, D5.5, J2.VBUS1, J2.VBUS2, J5.2, U2.1, U2.3
V_BATT: BT1.+, R28.1, U1.P36
V_RF: R17.2, U1.P7
WT+: J5.11, R35.1
WT_IN: R36.2, U4.P1
WT_OUT: R2.1, U$62.P4
WT_SCHMITT: R39.1, U4.P7, U$62.P2

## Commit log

2020-03-27 Adds breakout board and related documents, libraries
2020-03-27 Movies files out of "breakout" folder
2020-03-27 Renames files to correct module and BoB specification
2020-03-27 Renumbers parts, updates parts with PROD_IDs that didn't have them before
2020-03-28 Updates silk, fixes RF trace, moves some traces for better clearance
    * Fixes various small design issues
2020-03-30 Removes 0402 33 Ohm resistors in place of 33Ohm resistor bank
2020-03-30 Fixes packages with over sized tnames and tvalues
2020-03-30 Fixes more tvalues and tnames
2020-03-31 Adds custom silk
2020-03-31 Updates all parts to parts in Eagle Libraries
2020-03-31 Replaces 910 Ohm resistor with part in Eagle Library
2020-03-31 Replaces silk with coool skull
2020-03-31 Adds panel to files, deletes buzzard labels
2020-03-31 Adds silk for 3 axes and repanelizes
2020-04-03 Replaces 0.1uF 6.3V with the 0.1uF 10V X7R capacitors
2020-06-12 Add file names in .gitignore to ignore
2020-06-12 Adjust file name in .gitignore to ignore
2020-06-16 Fixes silk and repanelizes
2021-01-08 Adding u-blox Documents
2022-08-18 Updates silk, add new schmitt trigger package and symbol
    * Updates schematic layout
2022-08-30 Adds more capacitance to power lines
    * Fixes various trace irregularities
2022-08-30 Removes old design files(SparkFun.....), renames new design files (ZED-F9R v3)
2022-08-30 Adds new Production files and a few vias to the board design
2023-04-24 Updating ZED-F9R Datasheet
    Adding latest ZED-F9R datasheet release (April, 2023).
2023-04-24 Delete ZED-F9R_Datasheet_(UBX-19054459)
    Removing old ZED-F9R datasheet that was replaced with the latest release (April, 2023).
2023-06-12 Initial commit - swaps SMA connector with u.FL
2023-06-12 Removes older files, adds new measures and ordering instructions
2023-06-12 Adds new production panel
2023-06-13 Update README.md
    Adjust link for Arduino Library V3
2023-06-13 Update u-blox Integration Manual and Interface Descriptions for ZED-F9R-01B
2023-08-15 Adds u.FL version and moves all design files to their own folders
2023-08-15 Adds Production files for u.FL and organizes production folder with version sub-folders
2023-08-24 Update README.md
    Add both ZED-F9R versions in README.md
